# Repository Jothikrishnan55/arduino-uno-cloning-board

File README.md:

Arduino Uno Compatible Custom PCB

A minimal, custom-designed Arduino Uno-compatible microcontroller board built from scratch in KiCad, based on the ATmega328P microcontroller.

Overview

This project is a bare-bones recreation of the core Arduino Uno circuit — the same microcontroller, clock, and power system used in the official board, designed as a standalone PCB from the schematic level up. Unlike the original Arduino Uno, this board does not include an onboard USB-to-serial chip; programming is done externally through an ICSP header using a USBasp (or similar) programmer.

Components Used

Component	Value / Part	Function

U1	ATmega328P	Main microcontroller (runs the program)

Y1	16MHz Crystal	Provides clock timing for the microcontroller

C1, C2	22pF Ceramic Capacitors	Crystal load capacitors

C3, C4	100nF Ceramic Capacitors	Decoupling capacitors (VCC / AVCC noise filtering)

R1	10kΩ Resistor	Reset pull-up

SW1	Push Button	Manual reset switch

D1	LED	Power indicator

R2	220Ω Resistor	LED current-limiting resistor

U2	7805 Voltage Regulator	Converts 9–12V input to a stable 5V supply

C5	10µF Electrolytic Capacitor	Regulator input filter capacitor

C6	100nF Ceramic Capacitor	Regulator output filter capacitor

J1	Barrel Jack	9–12V DC power input

J2	2x3 Pin Header (ICSP)	Programming interface (MOSI, MISO, SCK, RESET, VCC, GND)

How It Works

Power supply: A 9–12V DC adapter connects through the barrel jack (J1) into a 7805 linear regulator (U2), which steps the voltage down to a stable 5V. Filter capacitors on both the input (C5) and output (C6) sides keep the supply clean.

Microcontroller: The regulated 5V powers the ATmega328P (U1) on its VCC and AVCC pins, each backed by a decoupling capacitor (C3, C4) to suppress noise.

Clock: A 16MHz crystal (Y1), paired with two 22pF load capacitors (C1, C2), gives the microcontroller its operating clock speed.

Reset circuit: A 10kΩ pull-up resistor (R1) holds the RESET pin high during normal operation; pressing the push button (SW1) pulls it low, resetting the chip.

Programming: Since there's no onboard USB interface, code is uploaded using an external ISP programmer connected to the 6-pin ICSP header (J2), which exposes the SPI programming pins (MOSI, MISO, SCK) along with RESET, VCC, and GND.

Status indicator: A power LED (D1) with a current-limiting resistor (R2) lights up whenever the board is powered.

Design Process

Schematic captured in KiCad, starting from individual component placement through to full net connections.

Verified using KiCad's Electrical Rules Checker (ERC) — 0 errors, 0 warnings.

PCB layout completed with component placement, routing, and a ground pour.

Verified using KiCad's Design Rules Checker (DRC) before generating manufacturing files.
Gerber files generated for fabrication.

Files Included

.kicad_sch — Schematic source file
.kicad_pcb — PCB layout file
.kicad_pro — KiCad project file
Gerber files — Ready for PCB manufacturing
Tools Used
KiCad — schematic capture, PCB layout, and Gerber generation
Status
Design complete and DRC/ERC clean. Not yet fabricated/tested on physical hardware.

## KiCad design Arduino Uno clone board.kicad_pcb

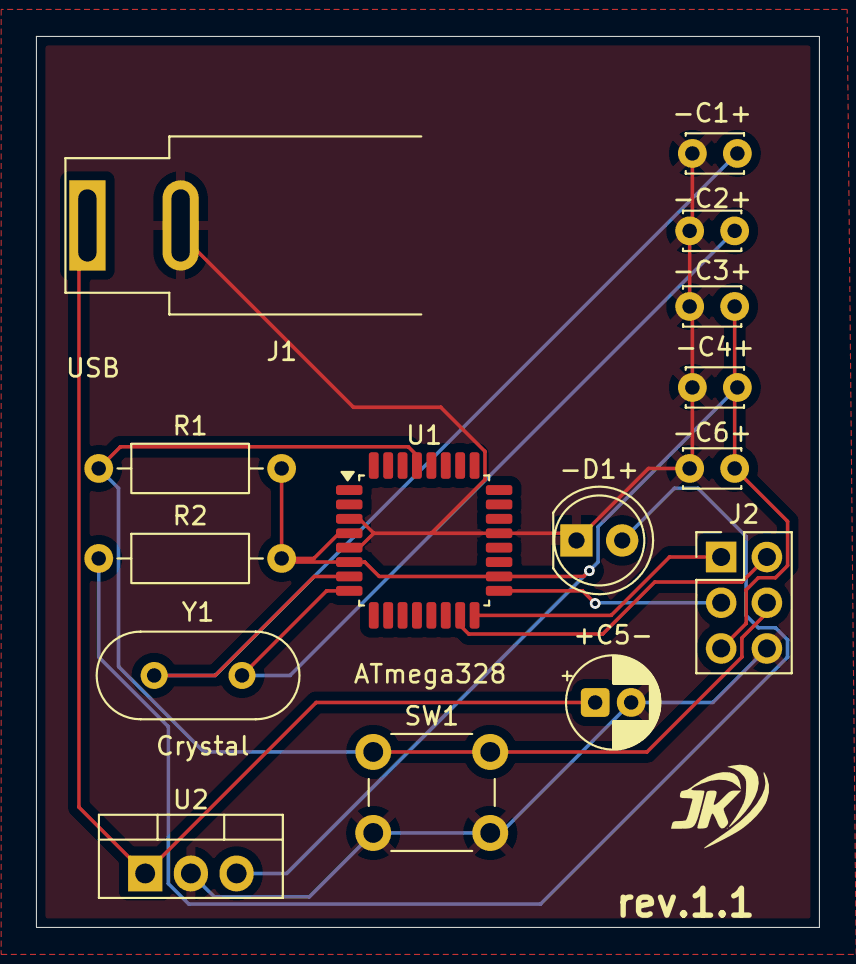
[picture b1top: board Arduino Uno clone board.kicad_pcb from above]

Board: 2 copper layers, 43.5 x 49.5 mm, 15 parts (0 on the bottom side), 10 nets.

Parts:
+C5-: 10uf; CP_Radial_D5.0mm_P2.00mm
-C1+, -C2+: 22pf; C_Disc_D3.0mm_W2.0mm_P2.50mm
-C3+, -C4+, -C6+: 100nf; C_Disc_D3.0mm_W2.0mm_P2.50mm
-D1+: LED; LED_D5.0mm
J1: Barrel_Jack; BarrelJack_SwitchcraftConxall_RAPC10U_Horizontal
J2: Conn_02x03_Odd_Even; PinHeader_2x03_P2.54mm_Vertical
R1: 10k; R_Axial_DIN0207_L6.3mm_D2.5mm_P10.16mm_Horizontal
R2: 220; R_Axial_DIN0207_L6.3mm_D2.5mm_P10.16mm_Horizontal
SW1: SW_Push; SW_PUSH_6mm
U1: ATmega328P-A; TQFP-32_7x7mm_P0.8mm
U2: L7805; TO-220-3_Vertical
Y1: Crystal; Crystal_HC49-4H_Vertical

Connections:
+5V: -C3+.2, -C4+.2, -C6+.1, J2.5, R1.2, R2.2, U1.4 (VCC), U1.6 (VCC), U1.18 (AVCC), U2.3 (OUT)
GND: +C5-.2, -C1+.1, -C2+.2, -C3+.1, -C4+.1, -C6+.2, -D1+.1 (K), J1.2, J2.6, SW1.2, U1.3 (GND), U1.5 (GND), U1.21 (GND), U2.2 (GND)
unnamed: -D1+.2 (A), R2.1
unnamed: J2.1, U1.16 (PB4)
unnamed: J2.2, U1.15 (PB3)
unnamed: J2.3, U1.17 (PB5)
unnamed: J2.4, R1.1, SW1.1, U1.29 (~RESET/PC6)
unnamed: -C1+.2, U1.7 (XTAL1/PB6), Y1.1
unnamed: -C2+.1, U1.8 (XTAL2/PB7), Y1.2
unnamed: +C5-.1, J1.1, U2.1 (IN)
